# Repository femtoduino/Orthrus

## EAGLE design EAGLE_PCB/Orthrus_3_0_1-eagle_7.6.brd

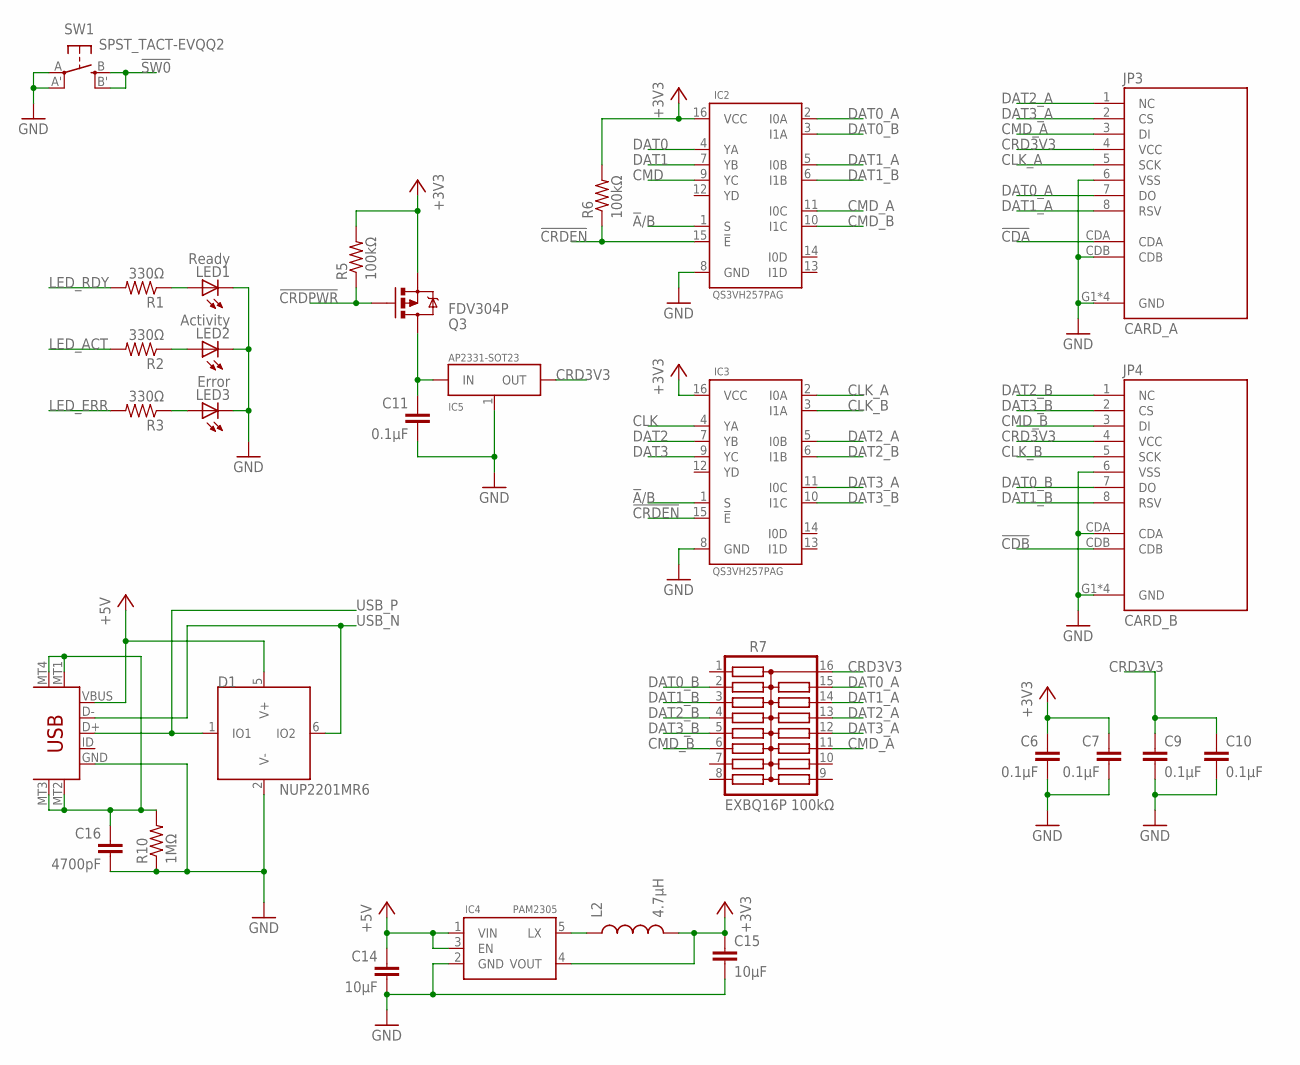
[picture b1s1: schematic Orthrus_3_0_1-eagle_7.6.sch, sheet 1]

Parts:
C6, C7, C9, C10, C11: 0.1µF; 0805
C14, C15: 10µF; 0805
C16: 4700pF; 0805
D1: NUP2201MR6; SOT23-6
IC2, IC3: QS3VH257PAG; TSSOP16
IC4: PAM2305; SOT23-5
IC5: AP2331-SOT23; SOT23-3
JP1: USB-5PIN-MICROB; USB-MICROB
JP3: CARD_A; DM3D-SF
JP4: CARD_B; DM3D-SF
L2: 4.7µH; 0805
LED1: Ready; CHIP-LED0805
LED2: Activity; CHIP-LED0805
LED3: Error; CHIP-LED0805
Q3: FDV304P; SOT23-3
R1, R2, R3: 330Ω; 0805
R5, R6: 100kΩ; 0805
R7: EXBQ16P 100kΩ; 4816P
R10: 1MΩ; 0805
SW1: SPST_TACT-EVQQ2; EVQ-Q2

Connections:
!A!/B: IC2.1 (S), IC3.1 (S); also elsewhere on the board
!CDA: JP3.CDA; also elsewhere on the board
!CDB: JP4.CDB; also elsewhere on the board
!CRDEN: IC2.15 (!E), IC3.15 (!E), R6.1; also elsewhere on the board
!CRDPWR: Q3.1 (G), R5.1; also elsewhere on the board
!SW0: SW1.B (S), SW1.B' (S1); also elsewhere on the board
+3V3: C6.1, C7.1, C15.1, IC2.16 (VCC), IC3.16 (VCC), IC4.4 (VOUT), L2.2, Q3.2 (S), R5.2, R6.2; also elsewhere on the board
+5V: C14.1, D1.5 (V+), IC4.1 (VIN), IC4.3 (EN), JP1.VBUS
CLK: IC3.4 (YA); also elsewhere on the board
CLK_A: IC3.2 (I0A), JP3.5 (SCK)
CLK_B: IC3.3 (I1A), JP4.5 (SCK)
CMD: IC2.9 (YC); also elsewhere on the board
CMD_A: IC2.11 (I0C), JP3.3 (DI), R7.11
CMD_B: IC2.10 (I1C), JP4.3 (DI), R7.6
CRD3V3: C9.1, C10.1, IC5.2 (OUT), JP3.4 (VCC), JP4.4 (VCC), R7.16
DAT0: IC2.4 (YA); also elsewhere on the board
DAT0_A: IC2.2 (I0A), JP3.7 (DO), R7.15
DAT0_B: IC2.3 (I1A), JP4.7 (DO), R7.2
DAT1: IC2.7 (YB); also elsewhere on the board
DAT1_A: IC2.5 (I0B), JP3.8 (RSV), R7.14
DAT1_B: IC2.6 (I1B), JP4.8 (RSV), R7.3
DAT2: IC3.7 (YB); also elsewhere on the board
DAT2_A: IC3.5 (I0B), JP3.1 (NC), R7.13
DAT2_B: IC3.6 (I1B), JP4.1 (NC), R7.4
DAT3: IC3.9 (YC); also elsewhere on the board
DAT3_A: IC3.11 (I0C), JP3.2 (CS), R7.12
DAT3_B: IC3.10 (I1C), JP4.2 (CS), R7.5
GND: C6.2, C7.2, C9.2, C10.2, C11.2, C14.2, C15.2, C16.2, D1.2 (V-), IC2.8 (GND), IC3.8 (GND), IC4.2 (GND), IC5.1 (GND), JP1.GND, JP3.6 (VSS), JP3.CDB, JP3.G1 (GND), JP3.G2 (GND), JP3.G3 (GND), JP3.G4 (GND), JP4.6 (VSS), JP4.CDA, JP4.G1 (GND), JP4.G2 (GND), JP4.G3 (GND), JP4.G4 (GND), LED1.C, LED2.C, LED3.C, R10.1, SW1.A, SW1.A' (P1); also elsewhere on the board
LED_ACT: R2.2; also elsewhere on the board
LED_ERR: R3.2; also elsewhere on the board
LED_RDY: R1.2; also elsewhere on the board
unnamed: IC4.5 (LX), L2.1
unnamed: C11.1, IC5.3 (IN), Q3.3 (D)
unnamed: C16.1, JP1.MT1 (MTN1), JP1.MT2 (MTN3), JP1.MT3 (MTN4), JP1.MT4 (MTN2), R10.2
unnamed: LED3.A, R3.1
unnamed: LED2.A, R2.1
unnamed: LED1.A, R1.1
USB_N: D1.6 (IO2), JP1.D-; also elsewhere on the board
USB_P: D1.1 (IO1), JP1.D+; also elsewhere on the board

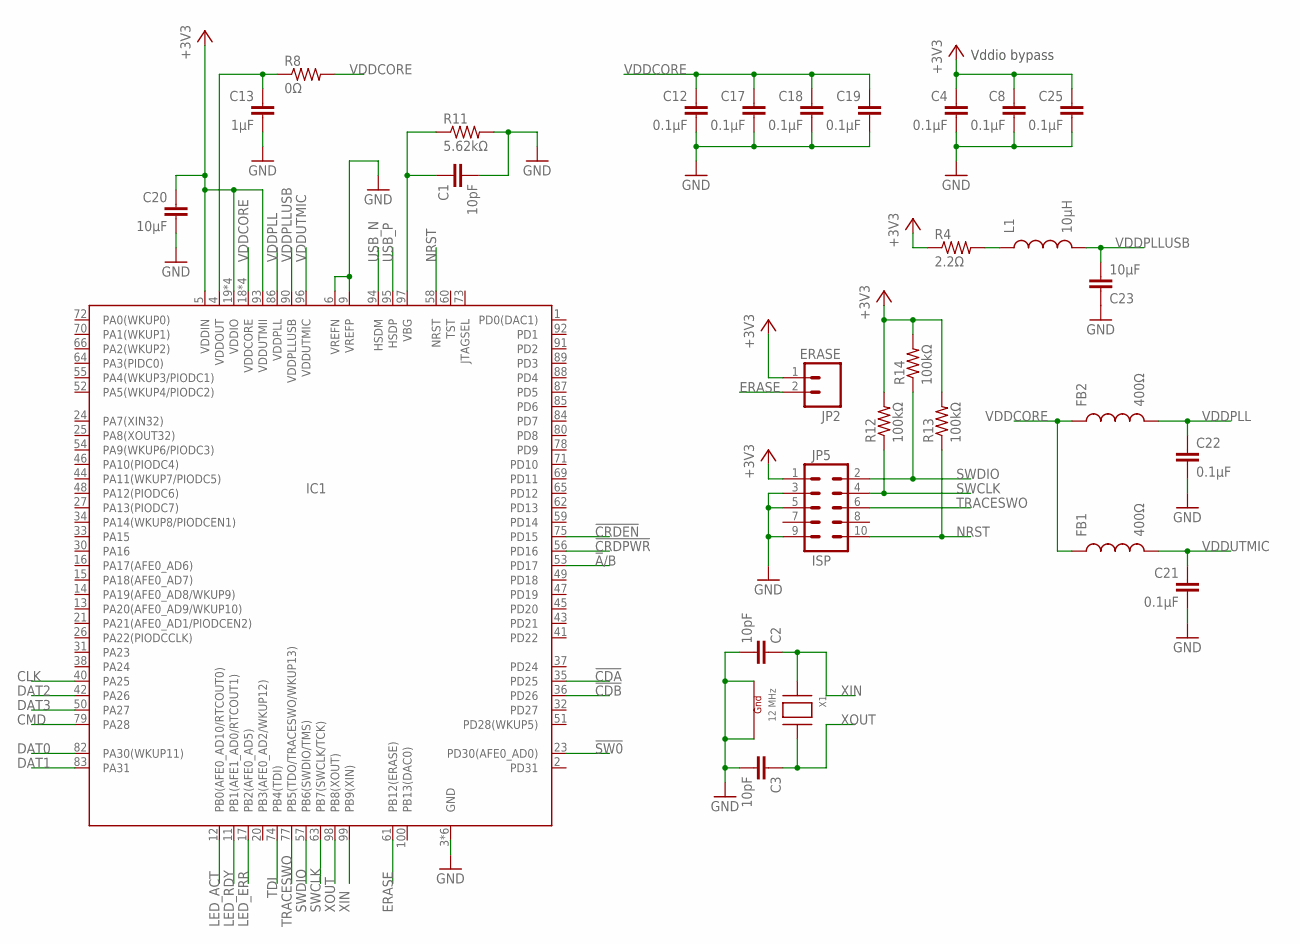
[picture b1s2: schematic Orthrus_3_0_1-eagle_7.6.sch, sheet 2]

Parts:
C1, C2, C3: 10pF; 0805
C4, C8, C12, C17, C18, C19, C21, C22, C25: 0.1µF; 0805
C13: 1µF; 0805
C20, C23: 10µF; 0805
FB1, FB2: 400Ω; 0805
IC1: ATSAMS70NXXAN; TQFP100
JP2: ERASE; 1X02
JP5: ISP; JTAGICE3-50MIL
L1: 10µH; 0805
R4: 2.2Ω; 0805
R8: 0Ω; 0805-WITH-JUMPER
R11: 5.62kΩ; 0805
R12, R13, R14: 100kΩ; 0805
X1: 12 MHz; NX3225

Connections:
!A!/B: IC1.53 (PD17); also elsewhere on the board
!CDA: IC1.35 (PD25); also elsewhere on the board
!CDB: IC1.36 (PD26); also elsewhere on the board
!CRDEN: IC1.75 (PD15); also elsewhere on the board
!CRDPWR: IC1.56 (PD16); also elsewhere on the board
!SW0: IC1.23 (PD30(AFE0_AD0)); also elsewhere on the board
+3V3: C4.1, C8.1, C20.1, C25.1, IC1.5 (VDDIN), IC1.19 (VDDIO), IC1.28 (VDDIO), IC1.68 (VDDIO), IC1.81 (VDDIO), IC1.93 (VDDUTMII), JP2.1, JP5.1, R4.1, R12.2, R13.2, R14.2; also elsewhere on the board
CLK: IC1.40 (PA25); also elsewhere on the board
CMD: IC1.79 (PA28); also elsewhere on the board
DAT0: IC1.82 (PA30(WKUP11)); also elsewhere on the board
DAT1: IC1.83 (PA31); also elsewhere on the board
DAT2: IC1.42 (PA26); also elsewhere on the board
DAT3: IC1.50 (PA27); also elsewhere on the board
ERASE: IC1.61 (PB12(ERASE)), JP2.2
GND: C1.2, C2.2, C3.2, C4.2, C8.2, C12.2, C13.2, C17.2, C18.2, C19.2, C20.2, C21.2, C22.2, C23.1, C25.2, IC1.3 (GND), IC1.6 (VREFN), IC1.7 (GND), IC1.8 (GND), IC1.9 (VREFP), IC1.10 (GND), IC1.29 (GND), IC1.67 (GND), JP5.3, JP5.5, JP5.9, R11.2, X1.2 (G2), X1.4 (G1); also elsewhere on the board
LED_ACT: IC1.12 (PB0(AFE0_AD10/RTCOUT0)); also elsewhere on the board
LED_ERR: IC1.17 (PB2(AFE0_AD5)); also elsewhere on the board
LED_RDY: IC1.11 (PB1(AFE1_AD0/RTCOUT1)); also elsewhere on the board
unnamed: C1.1, IC1.97 (VBG), R11.1
unnamed: L1.1, R4.2
unnamed: C13.1, IC1.4 (VDDOUT), R8.1
NRST: IC1.58 (NRST), JP5.10, R13.1
SWCLK: IC1.63 (PB7(SWCLK/TCK)), JP5.4, R12.1
SWDIO: IC1.57 (PB6(SWDIO/TMS)), JP5.2, R14.1
TDI: IC1.74 (PB4(TDI))
TRACESWO: IC1.77 (PB5(TDO/TRACESWO/WKUP13)), JP5.6
USB_N: IC1.94 (HSDM); also elsewhere on the board
USB_P: IC1.95 (HSDP); also elsewhere on the board
VDDCORE: C12.1, C17.1, C18.1, C19.1, FB1.1, FB2.1, IC1.18 (VDDCORE), IC1.22 (VDDCORE), IC1.39 (VDDCORE), IC1.76 (VDDCORE), R8.2
VDDPLL: C22.1, FB2.2, IC1.86 (VDDPLL)
VDDPLLUSB: C23.2, IC1.90 (VDDPLLUSB), L1.2
VDDUTMIC: C21.1, FB1.2, IC1.96 (VDDUTMIC)
XIN: C2.1, IC1.99 (PB9(XIN)), X1.1 (X1)
XOUT: C3.1, IC1.98 (PB8(XOUT)), X1.3 (X2)

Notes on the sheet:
Vddio bypass

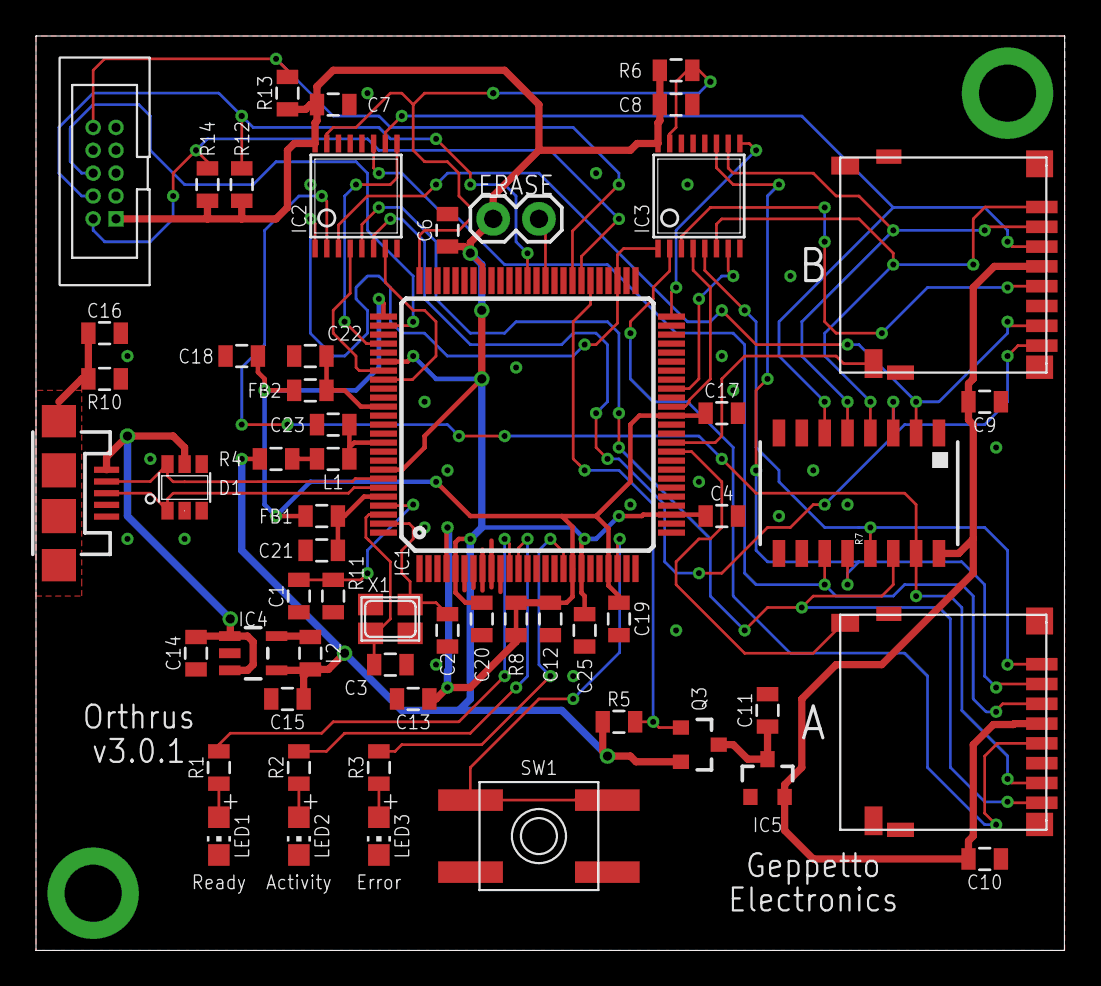
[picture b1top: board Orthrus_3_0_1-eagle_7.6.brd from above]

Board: 2 copper layers, 57.1 x 50.8 mm, 57 parts (0 on the bottom side), 53 nets.

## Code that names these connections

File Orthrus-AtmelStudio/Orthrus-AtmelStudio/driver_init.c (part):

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void MCI_0_PORT_init(void)
{

	gpio_set_pin_direction(PA28,
	                       // <y> Pin direction
	                       // <id> pad_direction
	                       // <GPIO_DIRECTION_OFF"> Off
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	                       // <GPIO_DIRECTION_OUT"> Out
	                       GPIO_DIRECTION_OUT);

	gpio_set_pin_level(PA28,
	                   // <y> Initial level
	                   // <id> pad_initial_level
	                   // <false"> Low
	                   // <true"> High
	                   false);

	gpio_set_pin_pull_mode(PA28,
	                       // <y> Pull configuration
	                       // <id> pad_pull_config
	                       // <GPIO_PULL_OFF"> Off
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	                       // <GPIO_PULL_DOWN"> Pull-down
	                       GPIO_PULL_OFF);

	gpio_set_pin_function(PA28,
	                      // <y> Pin function
	                      // <id> pad_function
	                      // <i> Auto : use driver pinmux if signal is imported by driver, else turn off function
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	                      // <GPIO_PIN_FUNCTION_D"> D
	                      PINMUX_PA28C_HSMCI_MCCDA);

	gpio_set_pin_direction(PA25,
	                       // <y> Pin direction
	                       // <id> pad_direction
	                       // <GPIO_DIRECTION_OFF"> Off
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	                       // <GPIO_DIRECTION_OUT"> Out
	                       GPIO_DIRECTION_OUT);

	gpio_set_pin_level(PA25,
	                   // <y> Initial level
	                   // <id> pad_initial_level
	                   // <false"> Low
	                   // <true"> High
	                   false);

	gpio_set_pin_pull_mode(PA25,
	                       // <y> Pull configuration
	                       // <id> pad_pull_config
	                       // <GPIO_PULL_OFF"> Off
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	                       // <GPIO_PULL_DOWN"> Pull-down
	                       GPIO_PULL_OFF);

	gpio_set_pin_function(PA25,
	                      // <y> Pin function
	                      // <id> pad_function
	                      // <i> Auto : use driver pinmux if signal is imported by driver, else turn off function
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	                      // <GPIO_PIN_FUNCTION_D"> D
	                      PINMUX_PA25D_HSMCI_MCCK);

	gpio_set_pin_direction(PA30,
	                       // <y> Pin direction
	                       // <id> pad_direction
	                       // <GPIO_DIRECTION_OFF"> Off
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	                       // <GPIO_DIRECTION_OUT"> Out
	                       GPIO_DIRECTION_OUT);

	gpio_set_pin_level(PA30,
	                   // <y> Initial level
	                   // <id> pad_initial_level
	                   // <false"> Low
	                   // <true"> High
	                   false);

	gpio_set_pin_pull_mode(PA30,
	                       // <y> Pull configuration
	                       // <id> pad_pull_config
	                       // <GPIO_PULL_OFF"> Off
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	                       // <GPIO_PULL_DOWN"> Pull-down
	                       GPIO_PULL_OFF);

	gpio_set_pin_function(PA30,
	                      // <y> Pin function
	                      // <id> pad_function
	                      // <i> Auto : use driver pinmux if signal is imported by driver, else turn off function
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	                      // <GPIO_PIN_FUNCTION_D"> D
	                      PINMUX_PA30C_HSMCI_MCDA0);

	gpio_set_pin_direction(PA31,
	                       // <y> Pin direction
	                       // <id> pad_direction
	                       // <GPIO_DIRECTION_OFF"> Off
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	                       // <GPIO_DIRECTION_OUT"> Out
	                       GPIO_DIRECTION_OUT);

	gpio_set_pin_level(PA31,
	                   // <y> Initial level
	                   // <id> pad_initial_level
	                   // <false"> Low
	                   // <true"> High
	                   false);

	gpio_set_pin_pull_mode(PA31,
	                       // <y> Pull configuration
	                       // <id> pad_pull_config
	                       // <GPIO_PULL_OFF"> Off
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	                       // <GPIO_PULL_DOWN"> Pull-down
	                       GPIO_PULL_OFF);

	gpio_set_pin_function(PA31,
	                      // <y> Pin function
	                      // <id> pad_function
	                      // <i> Auto : use driver pinmux if signal is imported by driver, else turn off function
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	                      // <GPIO_PIN_FUNCTION_D"> D
	                      PINMUX_PA31C_HSMCI_MCDA1);

	gpio_set_pin_direction(PA26,
	                       // <y> Pin direction
	                       // <id> pad_direction
	                       // <GPIO_DIRECTION_OFF"> Off
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	                       // <GPIO_DIRECTION_OUT"> Out
	                       GPIO_DIRECTION_OUT);

	gpio_set_pin_level(PA26,
	                   // <y> Initial level
	                   // <id> pad_initial_level
	                   // <false"> Low
	                   // <true"> High
	                   false);

	gpio_set_pin_pull_mode(PA26,
	                       // <y> Pull configuration
	                       // <id> pad_pull_config
	                       // <GPIO_PULL_OFF"> Off
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	                       // <GPIO_PULL_DOWN"> Pull-down
	                       GPIO_PULL_OFF);

	gpio_set_pin_function(PA26,
	                      // <y> Pin function
	                      // <id> pad_function
	                      // <i> Auto : use driver pinmux if signal is imported by driver, else turn off function
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	                      // <GPIO_PIN_FUNCTION_D"> D
	                      PINMUX_PA26C_HSMCI_MCDA2);

	gpio_set_pin_direction(PA27,
	                       // <y> Pin direction
	                       // <id> pad_direction
	                       // <GPIO_DIRECTION_OFF"> Off
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	                       // <GPIO_DIRECTION_OUT"> Out
	                       GPIO_DIRECTION_OUT);

	gpio_set_pin_level(PA27,
	                   // <y> Initial level
	                   // <id> pad_initial_level
	                   // <false"> Low
	                   // <true"> High
	                   false);

	gpio_set_pin_pull_mode(PA27,
	                       // <y> Pull configuration
	                       // <id> pad_pull_config
	                       // <GPIO_PULL_OFF"> Off
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	                       // <GPIO_PULL_DOWN"> Pull-down
	                       GPIO_PULL_OFF);

	gpio_set_pin_function(PA27,
	                      // <y> Pin function
	                      // <id> pad_function
	                      // <i> Auto : use driver pinmux if signal is imported by driver, else turn off function
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	/* Disable Watchdog */
	hri_wdt_set_MR_WDDIS_bit(WDT);

	/* GPIO on PB0 */

	// Set pin direction to output
	gpio_set_pin_direction(LED_ACT, GPIO_DIRECTION_OUT);

	gpio_set_pin_level(LED_ACT,
	                   // <y> Initial level
	                   // <id> pad_initial_level
	                   // <false"> Low
	                   // <true"> High
	                   false);

	gpio_set_pin_function(LED_ACT, GPIO_PIN_FUNCTION_OFF);

	/* GPIO on PB1 */

	// Set pin direction to output
	gpio_set_pin_direction(LED_RDY, GPIO_DIRECTION_OUT);

	gpio_set_pin_level(LED_RDY,
	                   // <y> Initial level
	                   // <id> pad_initial_level
	                   // <false"> Low
	                   // <true"> High
	                   false);

	gpio_set_pin_function(LED_RDY, GPIO_PIN_FUNCTION_OFF);

	/* GPIO on PB2 */

	// Set pin direction to output
	gpio_set_pin_direction(LED_ERR, GPIO_DIRECTION_OUT);

	gpio_set_pin_level(LED_ERR,
	                   // <y> Initial level
	                   // <id> pad_initial_level
	                   // <false"> Low
	                   // <true"> High
	                   false);

	gpio_set_pin_function(LED_ERR, GPIO_PIN_FUNCTION_OFF);

	/* GPIO on PB3 */

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
	gpio_set_pin_function(BUTTON, GPIO_PIN_FUNCTION_OFF);

	/* GPIO on PD15 */

	// Set pin direction to output
	gpio_set_pin_direction(CARD_EN, GPIO_DIRECTION_OUT);
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
	gpio_set_pin_function(CARD_EN, GPIO_PIN_FUNCTION_OFF);

	/* GPIO on PD16 */

	// Set pin direction to output
	gpio_set_pin_direction(CARD_PWR, GPIO_DIRECTION_OUT);
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
	gpio_set_pin_function(CARD_PWR, GPIO_PIN_FUNCTION_OFF);

	/* GPIO on PD17 */

	// Set pin direction to output
	gpio_set_pin_direction(AB_SELECT, GPIO_DIRECTION_OUT);
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
	gpio_set_pin_function(AB_SELECT, GPIO_PIN_FUNCTION_OFF);

	/* GPIO on PD25 */

	// Set pin direction to input
	gpio_set_pin_direction(CARD_DETECT_A, GPIO_DIRECTION_IN);
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
	gpio_set_pin_function(CARD_DETECT_A, GPIO_PIN_FUNCTION_OFF);

	/* GPIO on PD26 */

	// Set pin direction to input
	gpio_set_pin_direction(CARD_DETECT_B, GPIO_DIRECTION_IN);
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
	gpio_set_pin_function(CARD_DETECT_B, GPIO_PIN_FUNCTION_OFF);

	/* GPIO on PD30 */

	// Set pin direction to input
	gpio_set_pin_direction(BUTTON_ALT, GPIO_DIRECTION_IN);
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
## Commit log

2017-10-02 Inititial Atmel Studio setup
2017-10-02 Overlayed the Orthrus C and Header files into the Atmel Studio project structure
2017-10-04 Adding EAGLE PCB board files (Eagle 8.x and 7.6)
2017-10-04 Moving files to new location

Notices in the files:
parts and their libraries:
SparkFun-Capacitors: Licensing: CC v3.0 Share-Alike You are welcome to use this library for commercial purposes.
